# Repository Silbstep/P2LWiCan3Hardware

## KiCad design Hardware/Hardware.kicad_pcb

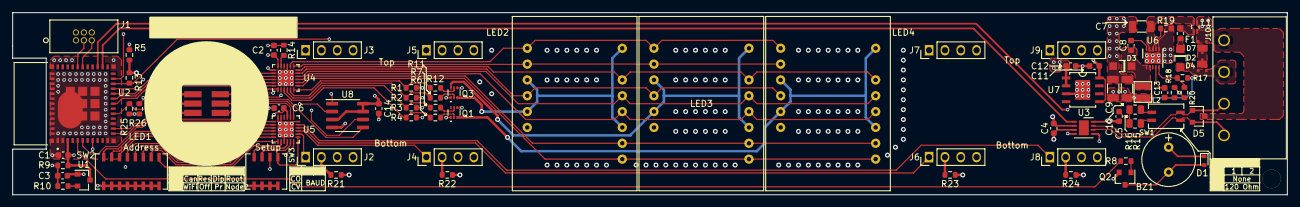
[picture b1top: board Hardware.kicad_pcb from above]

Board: 4 copper layers, 204.5 x 29.2 mm, 79 parts (0 on the bottom side), 83 nets.

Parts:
BZ1: GT-0903A
C1, C3, C11, C12: 1uF; C_0603_1608Metric
C2, C4, C6, C8, C14: 100nF; C_0603_1608Metric
C5: 4.7nF; C_0603_1608Metric
C7: 10uF; C_1206_3216Metric
C9, C10: 22uF; C_1206_3216Metric
C13: 330pF; C_0603_1608Metric
D1: 1N4148X; D_SOD-523
D2, D3: SL36PL-TP; SOD123-FL
D4, D7: PTVS24VU1UPA; PTVS10VU1UPAZ
D5: RESD1CANYT116; SOT-23
F1: 0.5A; Fuse_0603_1608Metric
H1: MountingHole; MountingHole_3mm_Pad
J1: EspressifMon; 3220-06-0100-00
J2, J3, J4, J5, J6, J7, J8, J9: Conn_01x04(P2L); PinHeader_1x04_P2.54mm_Vertical_NoConn
J10: 1757268; OQ0454510000G
L1: ACM-0603-121-T‎; ACM0603
L2: 15uH; MPL-SE2512
LED1: LED150505; 150505M173300
LED2, LED3, LED4: SA08-11EWA; SA08-11
Q1, Q3: NTZD3152PT1G
Q2: NX7002BKR; SOT-23
R1, R2, R3, R4: 162; R_0603_1608Metric
R5: 0; R_0603_1608Metric
R6, R7, R11, R12: 56; R_0603_1608Metric
R8: 100; R_0603_1608Metric
R9, R13: 10K; R_0603_1608Metric
R10: 1K; R_0603_1608Metric
R14: 3K; R_0603_1608Metric
R15, R16: 60; R_0805_2012Metric
R17: 210K; R_0603_1608Metric
R18: 47.5K; R_0603_1608Metric
R19: 100K; R_0603_1608Metric
R20: 40.2K; R_0603_1608Metric
R21, R22, R23, R24: 42.2; R_0603_1608Metric
R25, R26: 4K7; R_0603_1608Metric
SW1: CHS-08TA_NDC; CHS-02TA
SW2: CHS-08TA_NDC; CHS-08TA
SW3: CHS-08TA_NDC; CHS-04TA
U1: TCM809; SOT-23
U2: ESP32-C3-MINI(P2L); ESP32-C3-MINI-1-N4
U3: TJA1042TK; DFN-8-1EP_3x3mm_P0.65mm_EP1.6x2.40mm
U4: CAT4016HV6(P2L); CAT4016HV6-GT2
U5: XRA1201; XRA1403IL24-F
U6: MP4559DQ; DFN-10-1EP_3x3mm_P0.5mm_EP1.7x2.5mm
U7: BD33IA5MEFJ-ME2
U8: MB85RS16; SOIC-8_3.9x4.9mm_P1.27mm

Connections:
+3V3: BZ1.1, C1.1, C2.1, C6.1, C12.1, C14.1, D1.1, R5.1, R9.1, R13.1, R21.1, R22.1, R23.1, R24.1, R25.1, R26.1, U1.3, U2.3, U3.5, U4.24, U5.21, U7.1, U7.2, U8.3, U8.7, U8.8
+5V: C4.1, C9.1, C10.1, C11.1, L2.2, LED1.2, LED1.4, LED1.6, Q1.1, Q1.4, Q3.1, Q3.4, R1.2, R2.2, R3.2, R4.2, R17.2, U3.3, U7.5, U7.8
+24V: C7.1, L1.2, U6.8, U6.9
/Buzzer: R8.1, U2.5
/CAN+: D5.1, J10.2, SW1.4, U3.7
/CAN-: D5.2, J10.1, SW1.3, U3.6
/CLK: U2.19, U4.3
/EN: C3.1, J1.1, R9.2, R10.2, U2.8
/FRCS: R13.2, U2.22, U8.1
/K1: J2.1, U5.14
/K2: J4.1, U5.15
/K3: J6.1, U5.16
/K4: J8.1, U5.17
/LE: U2.18, U4.4
/LEDB: LED1.1, U4.7
/LEDG: LED1.5, U4.5
/LEDR: LED1.3, U4.6
/MISO: U2.12, U8.2
/MOSI: U2.6, U8.5
/SCK: U2.13, U8.6
/SCL: R26.2, U2.21, U5.19
/SD: U2.20, U4.2
/SDA: R25.2, U2.16, U5.20
/SEG1: R1.1, R12.1, U4.12
/SEG1SW: LED2.3, LED2.5, LED2.11, LED2.16, Q3.3
/SEG2: R2.1, R11.1, U4.11
/SEG2SW: LED3.3, LED3.5, LED3.11, LED3.16, Q3.6
/SEG3: R3.1, R7.1, U4.10
/SEG3SW: LED4.3, LED4.5, LED4.11, LED4.16, Q1.3
/SEG4: R4.1, R6.1, U4.9
/V+: D2.2, D4.1, D4.2, J10.3
/a: LED2.1, LED3.1, LED4.1, U4.20
/b: LED2.14, LED3.14, LED4.14, U4.18
/c: LED2.12, LED3.12, LED4.12, U4.15
/d: LED2.10, LED3.10, LED4.10, U4.14
/dp: LED2.9, LED3.9, LED4.9, U4.13
/e: LED2.4, LED3.4, LED4.4, U4.17
/f: LED2.2, LED3.2, LED4.2, U4.19
/g: LED2.13, LED3.13, LED4.13, U4.16
EP: C1.2, C2.2, C3.2, C4.2, C5.2, C6.2, C7.2, C9.2, C10.2, C11.2, C12.2, C14.2, D3.2, J1.4, J2.3, J3.2, J4.3, J5.2, J6.3, J7.2, J8.3, J9.2, L1.3, Q2.2, R14.2, R18.2, R19.2, R20.2, SW2.1, SW2.2, SW2.3, SW2.4, SW2.5, SW2.6, SW2.7, SW2.8, SW3.1, SW3.2, SW3.3, SW3.4, U1.1, U2.1, U2.2, U2.11, U2.14, U2.36, U2.37, U2.38, U2.39, U2.40, U2.41, U2.42, U2.43, U2.44, U2.45, U2.46, U2.47, U2.48, U2.49_1, U2.49_2, U2.49_3, U2.49_4, U2.49_5, U2.49_6, U2.49_7, U2.49_8, U2.49_9, U2.50, U2.51, U2.52, U2.53, U3.2, U3.8, U4.1, U4.21, U4.25, U5.9, U5.18, U5.23, U5.24, U5.25, U6.6, U6.11, U7.3, U7.9, U8.4
GND1: D5.3, D7.1, D7.2, J10.4, L1.4
unnamed: BZ1.2, D1.2, Q2.3
unnamed: C5.1, R15.2, R16.1
unnamed: C8.1, U6.10
unnamed: C13.1, U6.4
unnamed: C13.2, R18.1
unnamed: D2.1, F1.2
unnamed: D4.3, D4.4, D7.3, D7.4
unnamed: F1.1, L1.1
unnamed: J1.2, R5.2
unnamed: J1.3, U2.31
unnamed: J1.5, U2.30
unnamed: J1.6, U2.23
unnamed: J2.2, R21.2
unnamed: J4.2, R22.2
unnamed: J6.2, R23.2
unnamed: J8.2, R24.2
unnamed: Q1.2, R6.2
unnamed: Q1.5, R7.2
unnamed: Q2.1, R8.2
unnamed: Q3.2, R11.2
unnamed: Q3.5, R12.2
unnamed: R10.1, U1.2
unnamed: R14.1, U4.23
unnamed: R15.1, SW1.2
unnamed: R16.2, SW1.1
unnamed: R17.1, R20.1, U6.5
unnamed: R19.1, U6.7
unnamed: SW2.9, U5.8
unnamed: SW2.10, U5.7
unnamed: SW2.11, U5.6
unnamed: SW2.12, U5.5
unnamed: SW2.13, U5.4
unnamed: SW2.14, U5.3
unnamed: SW2.15, U5.2
unnamed: SW2.16, U5.1
unnamed: SW3.5, U5.13
unnamed: SW3.6, U5.12
unnamed: SW3.7, U5.11
unnamed: SW3.8, U5.10
unnamed: U2.26, U3.1
unnamed: U2.27, U3.4
SW: C8.2, D3.1, L2.1, U6.1, U6.2

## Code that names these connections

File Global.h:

#ifndef __Global_h
#define __Global_h

//Define Inputs
#define KEY1 (gpio_num_t)3
#define KEY2 (gpio_num_t)7
#define BKEY1 BIT3
#define BKEY2 BIT7
//Define Outputs
#define Buzzer (gpio_num_t) 2
#define LEDG (gpio_num_t)0
#define LEDB (gpio_num_t)1
#define LEDR (gpio_num_t)10
#define CLK (gpio_num_t)5
#define OE (gpio_num_t)6
#define LE (gpio_num_t)4
#define SDO (gpio_num_t)7
#define BLEDG BIT0
#define BLEDB BIT1
#define BLEDR BIT10
#define BCLK BIT5
#define BOE BIT6
#define BLE BIT4
#define BSDO BIT7
#define I2C_MASTER_SDA_IO 18
#define I2C_MASTER_SCL_IO 19
//I2C 
#define I2C_MASTER_FREQ_HZ 400000
#define I2C_MASTER_TX_BUF_DISABLE 0     //I2C master doesn't need buffer
#define I2C_MASTER_RX_BUF_DISABLE 0     //I2C master doesn't need buffer
#define I2C_MASTER_TIMEOUT_MS 500
//Define timer values
#define TIMER_DIVIDER 10
#define TIMER_VALUE 511                 //interrupt every 63.874uS i.e. 1 / (80000000 / TIMER_DIVIDER / TIMER_VALUE). Default clock source is APB (80MHz)
//LED and 7 segment
#define SEGMENTS 4						//Number of 7 segment led's
#define FLASHCOUNT 107					//0.5s
#define POWERUPTIMEOUT 488				//2s
//Buzzer
#define BUZZERCOUNT 700
//Notes
#define A7 3520
#define B7 3951
#define C7 2093
#define D7 2349
#define E7 2637
#define F7 2794
#define G7 3136
//LEDC (used for buzzer)
#define LEDC_TIMER              LEDC_TIMER_1
#define LEDC_MODE               LEDC_LOW_SPEED_MODE
#define BUZZER                  (2) // Define the output GPIO
#define LEDC_CHANNEL            LEDC_CHANNEL_0
#define LEDC_DUTY_RES           LEDC_TIMER_13_BIT // Set duty resolution to 13 bits
#define LEDC_DUTY               (4095) // Set duty to 50%. ((2 ** 13) - 1) * 50% = 4095
#define LEDC_FREQUENCY          (2730) // Frequency in Hertz. 
//Circular buffer sizes
#define ROOTBUFFERSIZE 900
#define NODEBUFFERSIZE 900
#define ACTIONBUFFERSIZE 80
//Mode definitions
#define CAN false
#define WIFI true
//States
#define LOW 0
#define HIGH 1

#endif

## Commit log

2023-03-03 Hardware design for P2LWiCan3. Production version 1

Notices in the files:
parts and their libraries:
Copyright 2016 Accelerated Designs. All rights reserved.
